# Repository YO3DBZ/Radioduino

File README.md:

# Radioduino
Some arduino code for a superheterodyne receiver based on the SI5351 as a clock source (LO and BFO).

Originally designed as a cheap LARCSet mod to replace the LC oscillator, it derailed into a more general-purpose tool (for example as a signal generator). It was designed to be built with the minimum necessary to do such things. All you need is a rotary encoder, an I2C LCD, and the SI5351 module.

### How to connect the modules:
1. Connect the LCD to the I2C bus
2. Connect the SI5351 to the I2C bus
3. Connect rotary encoder's Clock, Data, and Switch to Arduino's pins 6, 7, and 8

To build the rest of the receiver, all you need is 2 mixers (one for the first IF and the other for the product detector), a crystal filter (for SSB), some amplifiers, etc.

### Things to do:
- [x] Add a way to change the bands
- [ ] Save the settings to EEPROM
- [ ] Add a way to change band pass filters / pull some pins high depending on the modulation
- [ ] Add CAT control
- [x] Maybe TX?
- [ ] S-meter support
- [ ] Write some documentation so that this project could be usable by someone else
- [x] Split mode(using rit&xit)
- [x] Rit
- [ ] Have clk1 90 degrees out of phase from clk0 for direct conversion
- [x] Larcset suport with usb and cw shift
- [ ] Better Ui and Ux

---
*Special thanks to Mihai YO3CPR and Florin YO3FLX.*

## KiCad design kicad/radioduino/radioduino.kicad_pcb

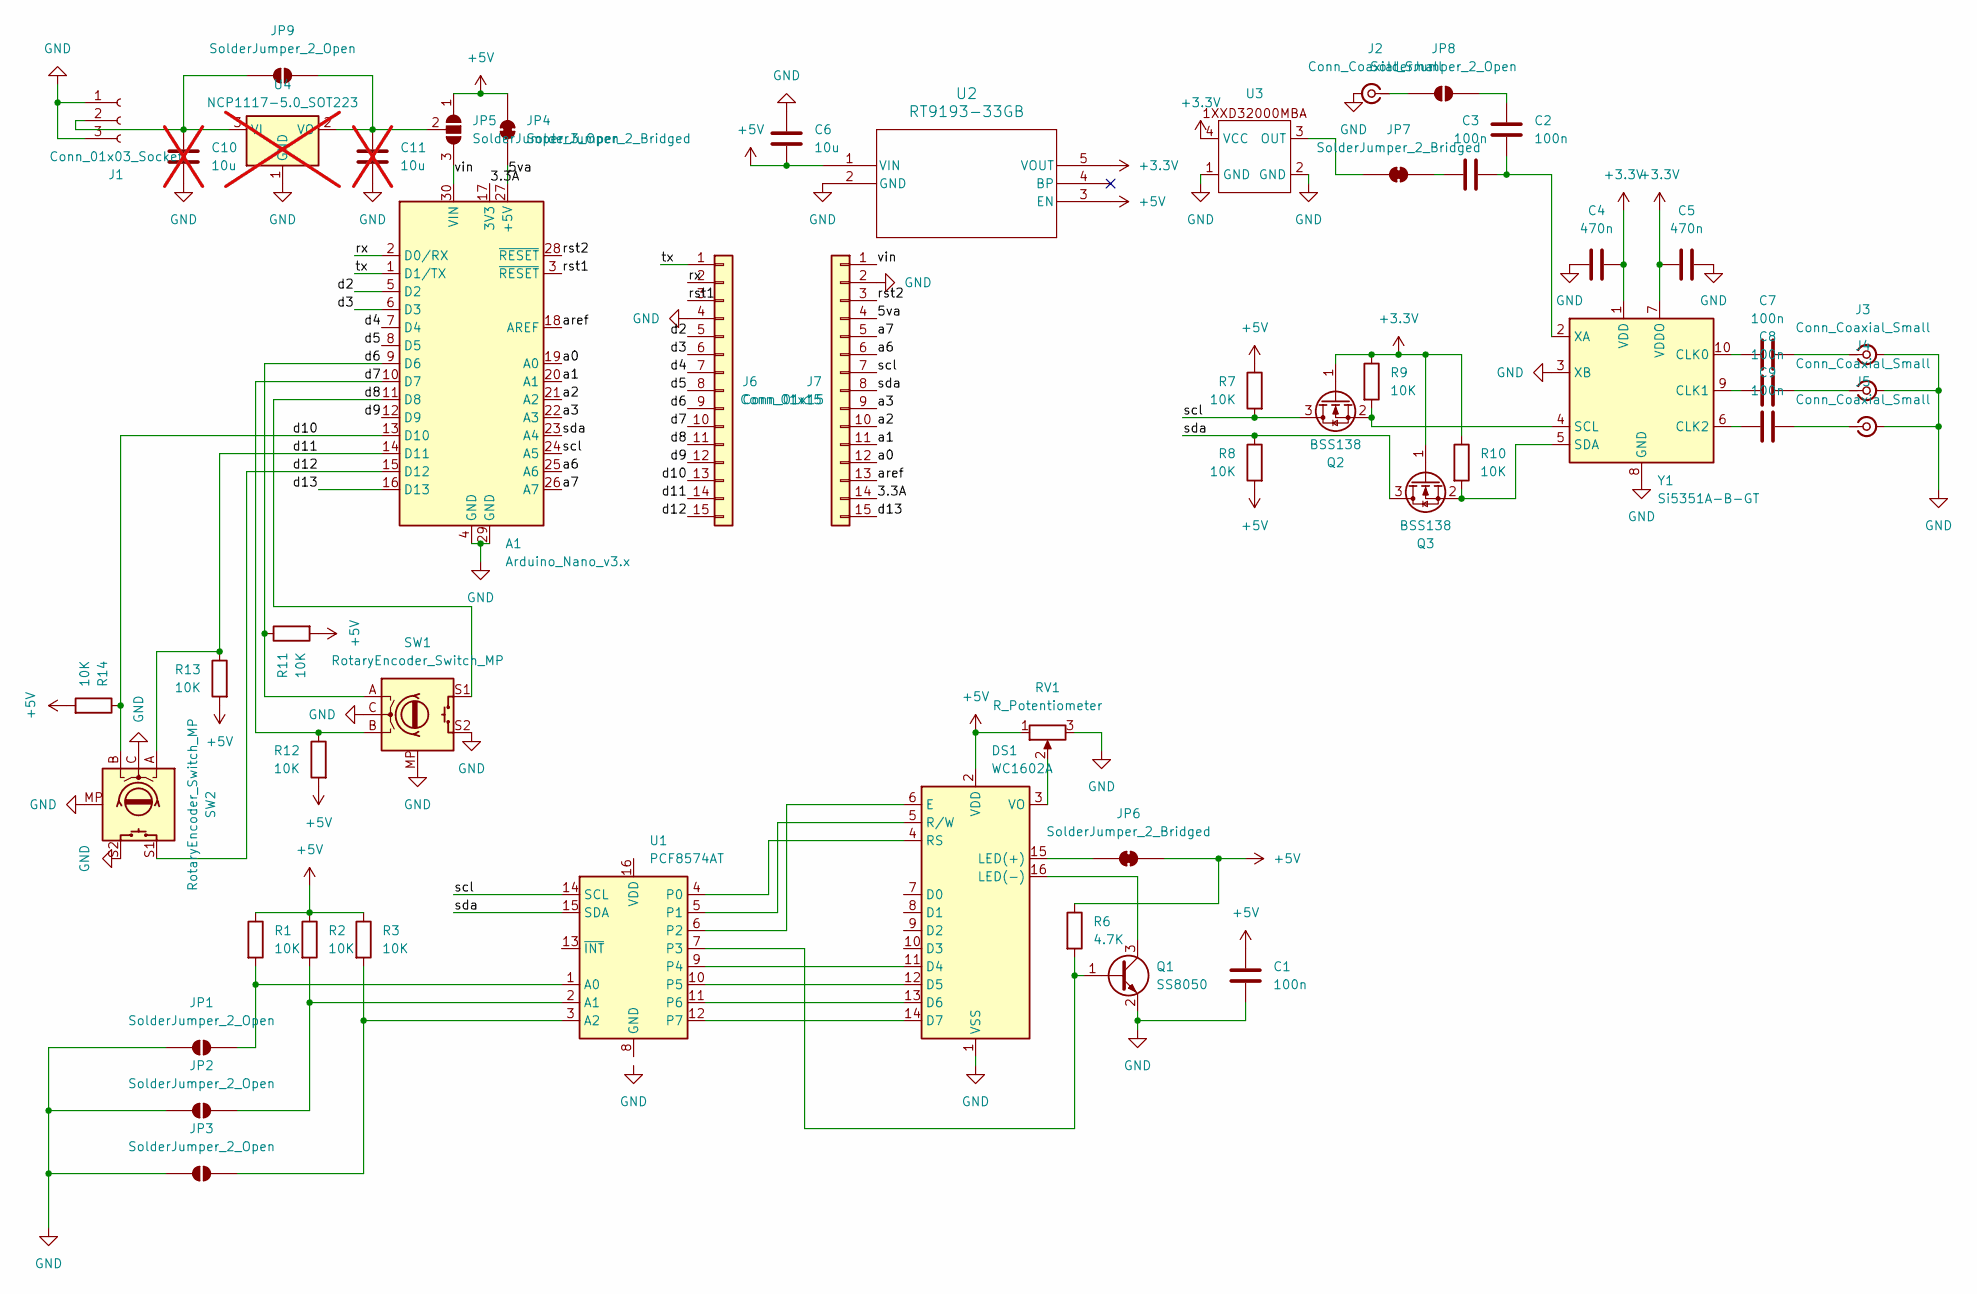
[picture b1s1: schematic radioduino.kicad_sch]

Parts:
A1: Arduino_Nano_v3.x; Arduino_Nano
C1, C2, C3, C7, C8, C9: 100n; C_0805_2012Metric
C4, C5: 470n; C_0805_2012Metric
C6: 10u; C_0805_2012Metric
C10, C11: 10u; C_0805_2012Metric; not fitted
DS1: WC1602A
J1: Conn_01x03_Socket; PinHeader_1x03_P2.54mm_Vertical
J2, J3, J4, J5: Conn_Coaxial_Small; SMA_Amphenol_132289_EdgeMount
J6, J7: Conn_01x15; PinHeader_1x15_P2.54mm_Vertical
JP1, JP2, JP3, JP8, JP9: SolderJumper_2_Open; SolderJumper-2_P1.3mm_Open_TrianglePad1.0x1.5mm
JP4, JP6, JP7: SolderJumper_2_Bridged; SolderJumper-2_P1.3mm_Bridged_Pad1.0x1.5mm
JP5: SolderJumper_3_Open; SolderJumper-3_P1.3mm_Open_Pad1.0x1.5mm
Q1: SS8050; SOT-23
Q2, Q3: BSS138; SOT-23
R1, R2, R3, R7, R8, R9, R10, R11, R12, R13, R14: 10K; R_0805_2012Metric_Pad1.20x1.40mm_HandSolder
R6: 4.7K; R_0805_2012Metric_Pad1.20x1.40mm_HandSolder
RV1: R_Potentiometer; Potentiometer_Runtron_RM-065_Vertical
SW1, SW2: RotaryEncoder_Switch_MP; RotaryEncoder_Alps_EC11E-Switch_Vertical_H20mm
U1: PCF8574AT; SOIC-16W_7.5x10.3mm_P1.27mm
U2: RT9193-33GB; SOT-23-5_RIT
U3: Crystal_SMD_2016-4Pin_2.0x1.6mm
U4: NCP1117-5.0_SOT223; SOT-223-3_TabPin2; not fitted
Y1: Si5351A-B-GT; MSOP-10_3x3mm_P0.5mm

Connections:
+3.3V: C4.2, C5.1, Q2.1 (G), Q3.1 (G), R9.1, R10.1, U2.5 (VOUT), U3.4 (VCC), Y1.1 (VDD), Y1.7 (VDDO)
+5V: C1.1, C6.1, DS1.2 (VDD), JP4.2 (B), JP5.1 (A), JP6.1 (A), R1.1, R2.1, R3.1, R6.1, R7.1, R8.2, R11.2, R12.2, R13.2, R14.2, RV1.1, U2.1 (VIN), U2.3 (EN)
/3.3A: A1.17 (3V3), J7.14
/5va: A1.27 (+5V), J7.4, JP4.1 (A)
/a0: A1.19 (A0), J7.12
/a1: A1.20 (A1), J7.11
/a2: A1.21 (A2), J7.10
/a3: A1.22 (A3), J7.9
/a6: A1.25 (A6), J7.6
/a7: A1.26 (A7), J7.5
/aref: A1.18 (AREF), J7.13
/d2: A1.5 (D2), J6.5
/d3: A1.6 (D3), J6.6
/d4: A1.7 (D4), J6.7
/d5: A1.8 (D5), J6.8
/d6: A1.9 (D6), J6.9, R11.1, SW1.A
/d7: A1.10 (D7), J6.10, R12.1, SW1.B
/d8: A1.11 (D8), J6.11, SW1.S1
/d9: A1.12 (D9), J6.12
/d10: A1.13 (D10), J6.13, R14.1, SW2.B
/d11: A1.14 (D11), J6.14, R13.1, SW2.A
/d12: A1.15 (D12), J6.15, SW2.S1
/d13: A1.16 (D13), J7.15
/rst1: A1.3 (~RESET), J6.3
/rst2: A1.28 (~RESET), J7.3
/rx: A1.2 (D0/RX), J6.2
/scl: A1.24 (A5), J7.7, Q2.3 (D), R7.2, U1.14 (SCL)
/sda: A1.23 (A4), J7.8, Q3.3 (D), R8.1, U1.15 (SDA)
/tx: A1.1 (D1/TX), J6.1
/vin: A1.30 (VIN), J7.1, JP5.3 (B)
GND: A1.4 (GND), A1.29 (GND), C1.2, C4.1, C5.2, C6.2, C10.1, C11.1, DS1.1 (VSS), J1.1, J1.3, J2.2 (Ext), J3.2 (Ext), J4.2 (Ext), J5.2 (Ext), J6.4, J7.2, JP1.1 (A), JP2.1 (A), JP3.1 (A), Q1.2 (E), RV1.3, SW1.C, SW1.MP, SW1.S2, SW2.C, SW2.MP, SW2.S2, U2.2 (GND), U3.1 (GND), U3.2 (GND), U4.1 (GND), Y1.3 (XB), Y1.8 (GND)
unnamed: DS1.11 (D4), U1.9 (P4)
unnamed: DS1.12 (D5), U1.10 (P5)
unnamed: DS1.13 (D6), U1.11 (P6)
unnamed: DS1.14 (D7), U1.12 (P7)
unnamed: DS1.6 (E), U1.6 (P2)
unnamed: DS1.15 (LED(+)), JP6.2 (B)
unnamed: DS1.16 (LED(-)), Q1.3 (C)
unnamed: DS1.4 (RS), U1.4 (P0)
unnamed: DS1.5 (R/W), U1.5 (P1)
unnamed: DS1.3 (VO), RV1.2
unnamed: C10.2, J1.2, JP9.1 (A), U4.3 (VI)
unnamed: J2.1 (In), JP8.1 (A)
unnamed: C7.2, J3.1 (In)
unnamed: C8.2, J4.1 (In)
unnamed: C9.2, J5.1 (In)
unnamed: JP1.2 (B), R1.2, U1.1 (A0)
unnamed: JP2.2 (B), R2.2, U1.2 (A1)
unnamed: JP3.2 (B), R3.2, U1.3 (A2)
unnamed: C11.2, JP5.2 (C), JP9.2 (B), U4.2 (VO)
unnamed: C3.1, JP7.1 (A)
unnamed: JP7.2 (B), U3.3 (OUT)
unnamed: C2.1, JP8.2 (B)
unnamed: Q1.1 (B), R6.2, U1.7 (P3)
unnamed: Q2.2 (S), R9.2, Y1.4 (SCL)
unnamed: Q3.2 (S), R10.2, Y1.5 (SDA)
unnamed: C7.1, Y1.10 (CLK0)
unnamed: C8.1, Y1.9 (CLK1)
unnamed: C9.1, Y1.6 (CLK2)
unnamed: C2.2, C3.2, Y1.2 (XA)

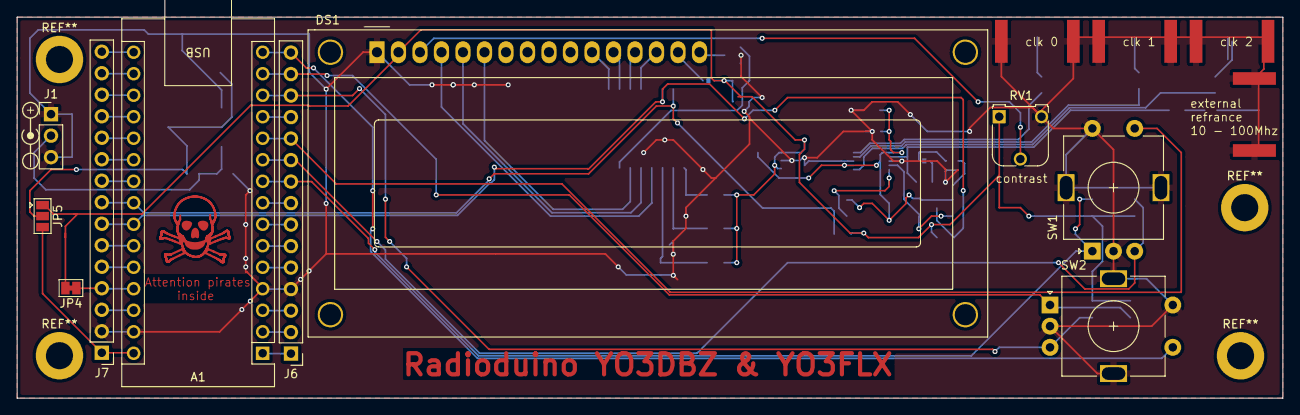
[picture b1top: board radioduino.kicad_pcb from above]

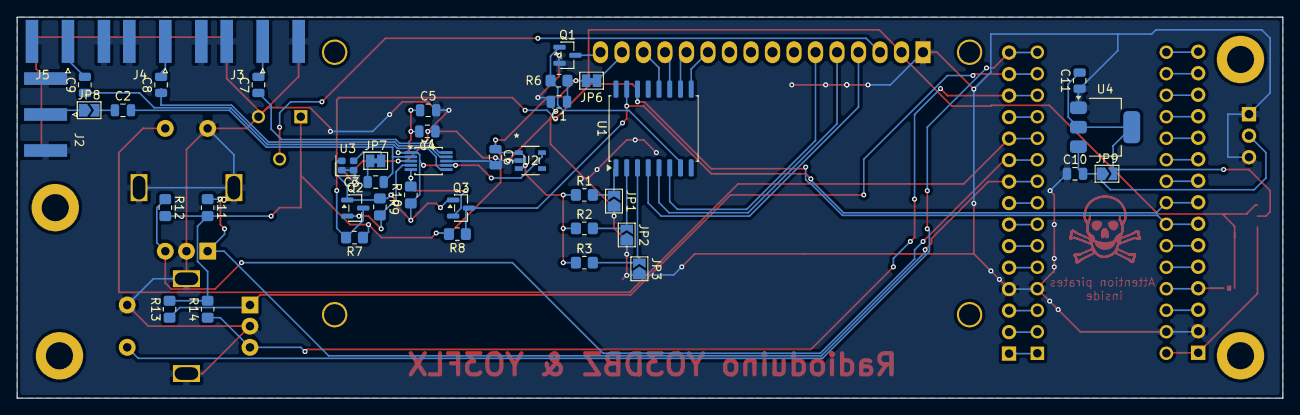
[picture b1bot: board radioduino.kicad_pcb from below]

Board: 2 copper layers, 149.5 x 45.0 mm, 52 parts (42 on the bottom side), 60 nets.

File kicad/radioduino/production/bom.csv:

Designator,Footprint,Quantity,Value,LCSC Part #
A1,Arduino_Nano,1,Arduino_Nano_v3.x,
"C1, C2, C3, C7, C8, C9",0805,6,100n,
"C10, C11, C6",0805,3,10u,
"C4, C5",0805,2,470n,
DS1,WC1602A,1,WC1602A,
J1,PinHeader_1x03_P2.54mm_Vertical,1,Conn_01x03_Socket,
"J2, J3, J4, J5",SMA_Amphenol_132289_EdgeMount,4,Conn_Coaxial_Small,
"J6, J7",PinHeader_1x15_P2.54mm_Vertical,2,Conn_01x15,
Q1,SOT-23,1,SS8050,
"Q2, Q3",SOT-23,2,BSS138,
"R1, R10, R11, R12, R2, R3, R7, R8, R9",0805,9,10K,
"R4, R5, R6",0805,3,4.7K,
RV1,Potentiometer_Runtron_RM-065_Vertical,1,R_Potentiometer,
SW1,RotaryEncoder_Alps_EC11E-Switch_Vertical_H20mm,1,RotaryEncoder_Switch_MP,
U1,SOIC-16W_7.5x10.3mm_P1.27mm,1,PCF8574AT,
U2,SOT-23-5_RIT,1,RT9193-33GB,
U3,Crystal_SMD_2016-4Pin_2.0x1.6mm,1,~,
U4,SOT-223-3_TabPin2,1,NCP1117-5.0_SOT223,
Y1,MSOP-10_3x3mm_P0.5mm,1,Si5351A-B-GT,
